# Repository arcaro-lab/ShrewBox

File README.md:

# ShrewBox: Modular Behavior Box for Tree Shrew and Other Small Animal Experiments

## Overview
We developed a low-cost, customizable behavior box designed for conducting animal experiments, particularly in tree shrews and other small animals. This modular platform allows precise control over stimulus presentation and reward delivery while animals maintain access to their home cage. It expands the methodological toolkit for investigating complex behaviors in a controlled yet naturalistic environment.

## Features
- **Precision Reward Delivery**: Stepper motors provide fine control (0.11° step rotation) of reward amounts with individual channel control, reducing wear and tear. These are downsized versions of the wonderful pumps developed by the Pachter Lab (https://github.com/pachterlab/pegasus).
- **Adjustable Visual Display**: Can accomodate 14"-15" monitors allowing for  adjustable viewing angles and distances ensure optimal stimulus presentation.
- **Capacitive Touch Pads**: Enables animals to indicate choices while maintaining gaze at the screen, allowing precise tracking of body position.
- **Compact and Integrated**: Raspberry Pi 4 replaces external computers, reducing footprint and minimizing the number of Arduinos and wires. All components are mounted directly on the box.
- **Customizable Box Panels**: Laser-cut and 3D-printable components simplify assembly while enabling modular expansion.
- **Scalability**: Daisy chain multiple behavior boxes to the same power source for simultaneous experiments.
- **Open-Source Experiment Control**: Runs on Python-based PsychoPy, making it accessible and customizable.
- **Integrated Weight Monitoring**: Onboard weight scale for tracking animal weight in real time.

## Assembly and Usage
We are currently developing detailed written instructions and instructional videos for assembling and using the behavior box. These will be available in this repository soon. In the meantime, groups interested in the behavior box should reach out to us directly for more information.

Currently, this repository provides:
- 3D files for 3D printing
- Files for laser-cut panels
- Bill of materials
- Source code for the capacitive touch sensor
- Source code for controlling Arduinos that interface with the stepper motor and weight sensors

## Photo

## Contributions
This project is open-source, and we welcome contributions! If you have improvements or modifications, feel free to submit a pull request or open an issue.

---
For inquiries, please contact the [Arcaro Lab](https://arcarolab.com).

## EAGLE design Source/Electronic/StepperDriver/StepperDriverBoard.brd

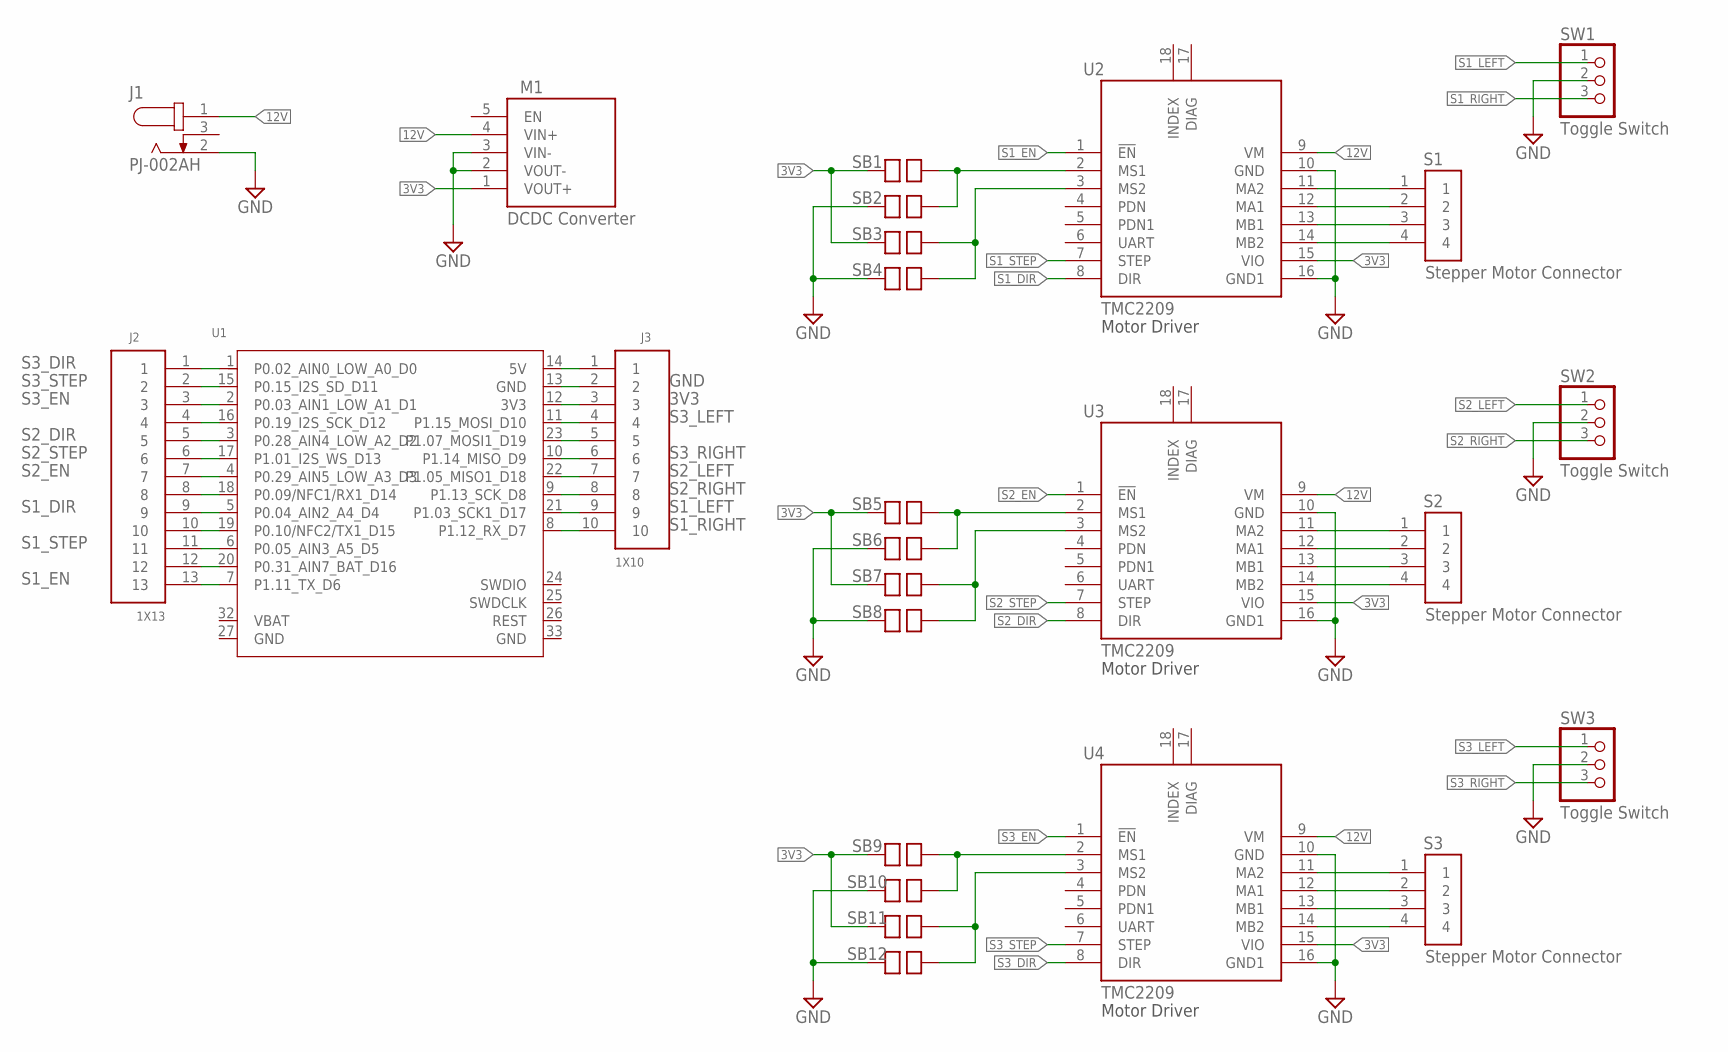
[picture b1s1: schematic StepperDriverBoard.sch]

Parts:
J1: PJ-002AH; CUI_PJ-002AH
J2: 1X13; 1X13-127MM
J3: 1X10; 1X10-127MM
M1: DCDC Converter; DROK_5V
S1, S2, S3: Stepper Motor Connector; 1X04-BIG
SB1, SB2, SB3, SB4, SB5, SB6, SB7, SB8, SB9, SB10, SB11, SB12: JUMPERP; JUMPER
SW1, SW2, SW3: Toggle Switch; 1X03
U1: XIAO-NRF52840_PLUS_SMDXIAO-NRF52840_PLUS; XIAO-NRF52840_PLUS_SMD
U2, U3, U4: TMC2209; MODULE_TMC2209_PINS

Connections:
3V3: J3.3, M1.1 (VOUT+), SB1.1, SB3.1, SB5.1, SB7.1, SB9.1, SB11.1, U1.12 (3V3), U2.15 (VIO), U3.15 (VIO), U4.15 (VIO)
12V: J1.1, M1.4 (VIN+), U2.9 (VM), U3.9 (VM), U4.9 (VM)
GND: J1.2, J3.2, M1.2 (VOUT-), M1.3 (VIN-), SB2.1, SB4.1, SB6.1, SB8.1, SB10.1, SB12.1, SW1.2, SW2.2, SW3.2, U1.13 (GND), U2.10 (GND), U2.16 (GND1), U3.10 (GND), U3.16 (GND1), U4.10 (GND), U4.16 (GND1)
unnamed: S2.1, U3.11 (MA2)
unnamed: S1.1, U2.11 (MA2)
unnamed: S1.2, U2.12 (MA1)
unnamed: S1.3, U2.13 (MB1)
unnamed: S1.4, U2.14 (MB2)
unnamed: SB1.2, SB2.2, U2.2 (MS1)
unnamed: SB3.2, SB4.2, U2.3 (MS2)
unnamed: S2.2, U3.12 (MA1)
unnamed: S2.3, U3.13 (MB1)
unnamed: S2.4, U3.14 (MB2)
unnamed: SB5.2, SB6.2, U3.2 (MS1)
unnamed: SB7.2, SB8.2, U3.3 (MS2)
unnamed: S3.1, U4.11 (MA2)
unnamed: S3.2, U4.12 (MA1)
unnamed: S3.3, U4.13 (MB1)
unnamed: S3.4, U4.14 (MB2)
unnamed: SB9.2, SB10.2, U4.2 (MS1)
unnamed: SB11.2, SB12.2, U4.3 (MS2)
unnamed: J2.10, U1.19 (P0.10/NFC2/TX1_D15)
unnamed: J2.8, U1.18 (P0.09/NFC1/RX1_D14)
unnamed: J2.12, U1.20 (P0.31_AIN7_BAT_D16)
unnamed: J2.4, U1.16 (P0.19_I2S_SCK_D12)
unnamed: J3.1, U1.14 (5V)
unnamed: J3.5, U1.23 (P1.07_MOSI1_D19)
S1_DIR: J2.9, U1.5 (P0.04_AIN2_A4_D4), U2.8 (DIR)
S1_EN: J2.13, U1.7 (P1.11_TX_D6), U2.1 (!EN)
S1_LEFT: J3.9, SW1.1, U1.21 (P1.03_SCK1_D17)
S1_RIGHT: J3.10, SW1.3, U1.8 (P1.12_RX_D7)
S1_STEP: J2.11, U1.6 (P0.05_AIN3_A5_D5), U2.7 (STEP)
S2_DIR: J2.5, U1.3 (P0.28_AIN4_LOW_A2_D2), U3.8 (DIR)
S2_EN: J2.7, U1.4 (P0.29_AIN5_LOW_A3_D3), U3.1 (!EN)
S2_LEFT: J3.7, SW2.1, U1.22 (P1.05_MISO1_D18)
S2_RIGHT: J3.8, SW2.3, U1.9 (P1.13_SCK_D8)
S2_STEP: J2.6, U1.17 (P1.01_I2S_WS_D13), U3.7 (STEP)
S3_DIR: J2.1, U1.1 (P0.02_AIN0_LOW_A0_D0), U4.8 (DIR)
S3_EN: J2.3, U1.2 (P0.03_AIN1_LOW_A1_D1), U4.1 (!EN)
S3_LEFT: J3.4, SW3.1, U1.11 (P1.15_MOSI_D10)
S3_RIGHT: J3.6, SW3.3, U1.10 (P1.14_MISO_D9)
S3_STEP: J2.2, U1.15 (P0.15_I2S_SD_D11), U4.7 (STEP)

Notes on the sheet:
Motor Driver

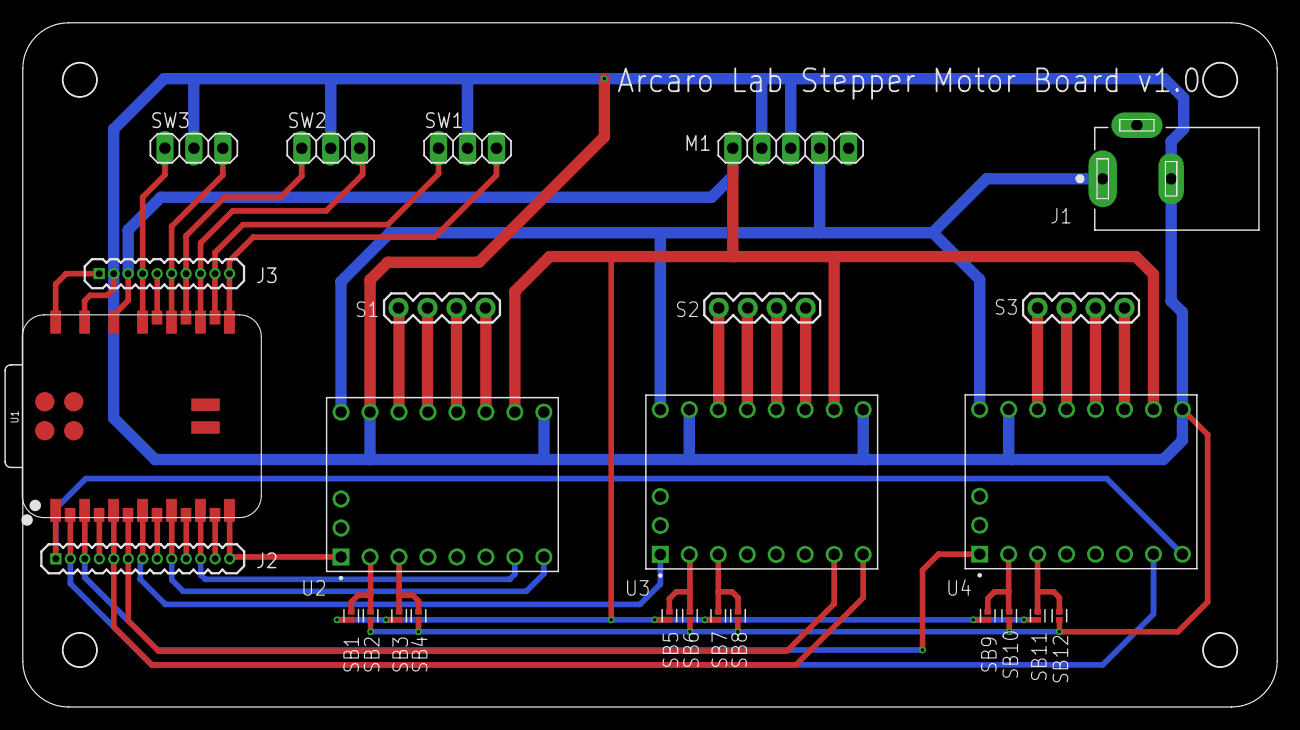
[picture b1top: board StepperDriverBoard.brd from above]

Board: 2 copper layers, 109.8 x 59.8 mm, 26 parts (0 on the bottom side), 42 nets.

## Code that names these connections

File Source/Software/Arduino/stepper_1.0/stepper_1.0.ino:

#include <Arduino.h>
#include <Adafruit_TinyUSB.h>  // OK to keep if your board uses TinyUSB (nRF52 Feather etc.)

// ===================== Pin assignments =====================
// Stepper 1
const int S1_DIR  = D4;
const int S1_STEP = D5;
const int S1_EN   = D6;

// Stepper 2
const int S2_DIR  = D2;
const int S2_STEP = D13;
const int S2_EN   = D3;

// Stepper 3
const int S3_DIR  = D0;
const int S3_STEP = D11;
const int S3_EN   = D1;

// Toggle inputs (active LOW with INPUT_PULLUP)
const int S1_LEFT  = D19;
const int S1_RIGHT = D7;

const int S2_LEFT  = D18;
const int S2_RIGHT = D8;

const int S3_LEFT  = D10;
const int S3_RIGHT = D9;

// ===================== Motion defaults =====================
// steps = number of step pulses
// sp_us = delayMicroseconds used for HIGH and LOW (half-period)
// Example: sp_us=400 => 800us per step => 1250 steps/sec (approx)
int defaultSteps = 100;
int defaultSpUs  = 400;

// ===================== Stepper description table =====================
struct StepperPins {
  int dir;
  int step;
  int en;
};

StepperPins motors[3] = {
  { S1_DIR, S1_STEP, S1_EN },
  { S2_DIR, S2_STEP, S2_EN },
  { S3_DIR, S3_STEP, S3_EN }
};

// ===================== Serial line input buffer =====================
static const size_t LINE_BUF_LEN = 64;
char lineBuf[LINE_BUF_LEN];
size_t lineLen = 0;

// --------------------- Helper: printLine ---------------------
template<typename T, typename... Types>
void printLine(T first, Types... other) {
  Serial.print(first);
  printLine(other...);
}
void printLine() { Serial.println(); }

// --------------------- Stepper low-level helpers ---------------------
void enableMotor(uint8_t idx, bool enable) {
  // Many TMC2209 breakouts use EN as active LOW.
  // Your original code sets EN LOW to enable, so we keep that.
  digitalWrite(motors[idx].en, enable ? LOW : HIGH);
}

void setDir(uint8_t idx, uint8_t dir01) {
  // Match your existing button behavior:
  // RIGHT used DIR=LOW, LEFT used DIR=HIGH.
  // Here: dir=0 (CW) -> LOW, dir=1 (CCW) -> HIGH.
  digitalWrite(motors[idx].dir, (dir01 == 0) ? LOW : HIGH);

  // If you need to flip CW/CCW meaning, swap the LOW/HIGH above.
}

void stepMotor(uint8_t idx, long steps, int sp_us) {
  if (idx >= 3) return;
  if (steps <= 0) return;
  if (sp_us < 2) sp_us = 2; // avoid too-small delays

  // Blocking pulse train (simple + reliable)
  for (long i = 0; i < steps; i++) {
    digitalWrite(motors[idx].step, HIGH);
    delayMicroseconds(sp_us);
    digitalWrite(motors[idx].step, LOW);
    delayMicroseconds(sp_us);
  }
}

// ===================== Serial command parsing =====================
// Supported commands:
//
//   S1,0,100        -> motor 1, dir=0, steps=100 (uses defaultSpUs)
//   S2,1,200,300    -> motor 2, dir=1, steps=200, sp_us=300
//
// Also supports whitespace, and lowercase "s1" etc.

void handleCommand(char* cmd) {
  // Trim leading spaces
  while (*cmd == ' ' || *cmd == '\t' || *cmd == '\r' || *cmd == '\n') cmd++;
  if (*cmd == 0) return;

  // Quick help
  if (strcasecmp(cmd, "HELP") == 0) {
    printLine("Commands:");
    printLine("  S1,0,100         (motor 1, dir 0=CW, steps 100)");
    printLine("  S2,1,200,400     (motor 2, dir 1=CCW, steps 200, sp_us 400)");
    printLine("  POS?             (not implemented here)");
    return;
  }

  // Expect "S<id>,<dir>,<steps>[,<sp_us>]"
  // Example: "S1,0,100"
  if (tolower(cmd[0]) != 's') {
    printLine("ERR: command must start with S (try HELP)");
    return;
  }

  // Parse motor number after 'S'
  int motorId = cmd[1] - '0';   // '1'..'3'
  if (motorId < 1 || motorId > 3) {
    printLine("ERR: motor must be S1..S3");
    return;
  }
  uint8_t idx = (uint8_t)(motorId - 1);

  // Find first comma
  char* p = strchr(cmd, ',');
  if (!p) { printLine("ERR: format S1,dir,steps[,sp_us]"); return; }
  p++; // move past comma

  // Tokenize remaining fields by comma
  // dir
  char* tokDir = p;
  char* tokSteps = strchr(tokDir, ',');
  if (!tokSteps) { printLine("ERR: missing steps"); return; }
  *tokSteps = 0;
  tokSteps++;

  // steps
  char* tokSp = strchr(tokSteps, ',');
  int sp_us = defaultSpUs;
  if (tokSp) {
    *tokSp = 0;
    tokSp++;
    sp_us = atoi(tokSp);
  }

  int dir01 = atoi(tokDir);
  long steps = atol(tokSteps);

  if (!(dir01 == 0 || dir01 == 1)) {
    printLine("ERR: dir must be 0 or 1");
    return;
  }
  if (steps <= 0) {
    printLine("ERR: steps must be > 0");
    return;
  }

  // Execute
  enableMotor(idx, true);
  setDir(idx, (uint8_t)dir01);
  stepMotor(idx, steps, sp_us);

  printLine("OK: S", motorId, " dir=", dir01, " steps=", steps, " sp_us=", sp_us);
}

// Read serial bytes into a line buffer; process on newline
void pollSerial() {
  while (Serial.available()) {
    char c = (char)Serial.read();

    // End of line -> process
    if (c == '\n' || c == '\r') {
      if (lineLen > 0) {
        lineBuf[lineLen] = 0;  // null-terminate
        handleCommand(lineBuf);
        lineLen = 0;
      }
      continue;
    }

    // Normal char
    if (lineLen < (LINE_BUF_LEN - 1)) {
      lineBuf[lineLen++] = c;
    } else {
      // overflow: reset
      lineLen = 0;
      printLine("ERR: line too long");
    }
  }
}

// ===================== Setup / Loop =====================
void setup() {
  Serial.begin(57600);
  while (!Serial) { delay(10); }

  pinMode(LED_RED, OUTPUT);
  digitalWrite(LED_RED, LOW);

  // Motor pins
  for (int i = 0; i < 3; i++) {
    pinMode(motors[i].dir, OUTPUT);
    pinMode(motors[i].step, OUTPUT);
    pinMode(motors[i].en, OUTPUT);

    // Enable by default (your original behavior)
    enableMotor(i, true);
  }

  // Buttons
  pinMode(S1_LEFT,  INPUT_PULLUP);
  pinMode(S1_RIGHT, INPUT_PULLUP);
  pinMode(S2_LEFT,  INPUT_PULLUP);
  pinMode(S2_RIGHT, INPUT_PULLUP);
  pinMode(S3_LEFT,  INPUT_PULLUP);
  pinMode(S3_RIGHT, INPUT_PULLUP);

  printLine("Started. Type HELP. Serial format: S1,0,100 or S2,1,200,400");
}

void loop() {
  pollSerial();

  // ---------- Existing button behavior ----------
  if (digitalRead(S1_LEFT) == LOW) {
    digitalWrite(motors[0].dir, HIGH);
    stepMotor(0, defaultSteps, defaultSpUs);
    printLine("BTN: S1_LEFT");
  } else if (digitalRead(S1_RIGHT) == LOW) {
    digitalWrite(motors[0].dir, LOW);
    stepMotor(0, defaultSteps, defaultSpUs);
    printLine("BTN: S1_RIGHT");
  }

  if (digitalRead(S2_LEFT) == LOW) {
    digitalWrite(motors[1].dir, HIGH);
    stepMotor(1, defaultSteps, defaultSpUs);
    printLine("BTN: S2_LEFT");
  } else if (digitalRead(S2_RIGHT) == LOW) {
    digitalWrite(motors[1].dir, LOW);
    stepMotor(1, defaultSteps, defaultSpUs);
    printLine("BTN: S2_RIGHT");
  }

  if (digitalRead(S3_LEFT) == LOW) {
    digitalWrite(motors[2].dir, HIGH);
    stepMotor(2, defaultSteps, defaultSpUs);
    printLine("BTN: S3_LEFT");
  } else if (digitalRead(S3_RIGHT) == LOW) {
    digitalWrite(motors[2].dir, LOW);
    stepMotor(2, defaultSteps, defaultSpUs);
    printLine("BTN: S3_RIGHT");
  }
}

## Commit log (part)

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2025-03-05 Initial Commit
    Create project for ShrewBox Design
2025-03-06 Updated BOM and added 3D file for Carriage
2025-09-09 Create BillOfMaterials_v2.xlsx
    Added materials for new pump
2026-02-04 Update files for syringe pump, panels. Added PCB files for Stepper Driver
2026-02-04 added gitignore
2026-02-05 Corrected the thickness of Acrylic Sheets in BOM
2026-02-06 Updated stepper and scale software
2026-06-25 Updated LaserCutPanels
    Enlarged the EBox
    Shorten the WeightFloor
    Corrected BottomGuide
2026-06-30 Update GuardPanel.dxf
    Make GuardPanel fit into 12 inch acrylic sheet
